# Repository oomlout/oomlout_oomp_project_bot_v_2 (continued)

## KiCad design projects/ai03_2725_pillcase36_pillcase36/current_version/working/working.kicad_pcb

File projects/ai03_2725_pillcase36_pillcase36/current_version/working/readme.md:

# pillcase36
 
## summary 
* id: ai03_2725_pillcase36_pillcase36
* user: ai03_2725
* name: pillcase36
* board: pillcase36
* repo: https://github.com/ai03-2725/pillcase36
* src_file_repo_kicad_pcb: pillcase36.kicad_pcb
* src_file_repo_kicad_pcb_link: https://github.com/ai03-2725/pillcase36/tree/master/pillcase36.kicad_pcb

* src_file_repo_sch: pillcase36.sch
* src_file_repo_sch_link: https://github.com/ai03-2725/pillcase36/tree/master/pillcase36.sch
* full details link: https://github.com/oomlout/oomlout_oomp_project_bot_v_2/tree/main/projects/ai03_2725_pillcase36_pillcase36/current_version/working  

## schematic  
  
[schematic (pdf)](working_schematic.pdf) 

## pcb  

[board (pdf)](working.pdf)  

## working_bom
| Id | Designator | Footprint | Quantity | Designation | Supplier and ref |  | None | 
| --- | --- | --- | --- | --- | --- | --- | --- | 
| 1 | D1,D2,D3,D4,D5,D7,D8,D9,D10,D11,D12,D13,D14,D15,D16,D17,D18,D19,D20,D21,D22,D23,D24,D25,D26,D27,D28,D29,D30,D31,D32,D33,D34,D35,D36,D6 | Diode_SMD_THT_N | 36 | D |  |  | [''] | 
| 2 | J1 | trrs_jack_aki_flip | 1 | AudioJack4_Ground |  |  | [''] | 
| 3 | R2,R1 | Resister_SMD_THT_N | 2 | 10K |  |  | [''] | 
| 4 | SW1,SW2,SW3,SW4,SW5,SW6,SW7,SW8,SW9,SW10,SW11,SW12,SW13,SW14,SW15,SW16,SW17,SW18,SW19,SW20,SW21,SW22,SW23,SW24,SW25,SW26,SW27,SW28,SW29,SW30,SW31,SW32,SW33,SW34,SW35,SW36 | key_switch_mx | 36 | SW_Push |  |  | [''] | 
| 5 | RESET | SW_PUSH_6mm_h5mm | 1 | SW_Push |  |  | [''] | 
| 6 | U1 | BlackPill | 1 | BlackPill |  |  | [''] | 
| 7 |  | Hole_5mm | 1 |  |  |  | [''] | 
| 8 | G***,G*** | pillcase36_logo | 2 | pillcase36_logo |  |  | [''] | 
| 9 | U2 | SOIC-8-N | 1 | 24LC00 |  |  | [''] | 
| 10 | SCL1 ,SDA1 | JP | 2 | SolderJumper_2_Bridged |  |  | [''] | 
| 11 | 0.1u | C_0603 | 1 | C |  |  | [''] | 

## bom_schematic
| Ref | Qnty | Value | Cmp name | Footprint | Description | Vendor | DNP | 
| --- | --- | --- | --- | --- | --- | --- | --- | 
| 0.1u1 | 1 | C | C | Capacitors_SMD:C_0603 | Unpolarized capacitor |  |  | 
| D1, D2, D3, D4, D5, D6, D7, D8, D9, D10, D11, D12, D13, D14, D15, D16, D17, D18, D19, D20, D21, D22, D23, D24, D25, D26, D27, D28, D29, D30, D31, D32, D33, D34, D35, D36 | 36 | D | D | pillcase36:Diode_SMD_THT_N | Diode |  |  | 
| J1 | 1 | AudioJack4_Ground | AudioJack4_Ground-Connector | pillcase36:trrs_jack_aki_flip |  |  |  | 
| JP13, JP14 | 2 | SolderJumper_2_Bridged | SolderJumper_2_Bridged | pillcase36:JP | Solder Jumper, 2-pole, closed/bridged |  |  | 
| R1, R2 | 2 | 10K | R | pillcase36:Resister_SMD_THT_N | Resistor |  |  | 
| SW1, SW2, SW3, SW4, SW5, SW6, SW7, SW8, SW9, SW10, SW11, SW12, SW13, SW14, SW15, SW16, SW17, SW18, SW19, SW20, SW21, SW22, SW23, SW24, SW25, SW26, SW27, SW28, SW29, SW30, SW31, SW32, SW33, SW34, SW35, SW36 | 36 | SW_Push | SW_Push | pillcase36:key_switch_mx | Push button switch, generic, two pins |  |  | 
| SW37 | 1 | SW_Push | SW_Push | Buttons_Switches_THT:SW_PUSH_6mm_h5mm | Push button switch, generic, two pins |  |  | 
| TP1 | 1 | B13 | TestPoint | Measurement_Points:Measurement_Point_Round-TH_Small | test point |  |  | 
| TP2 | 1 | B15 | TestPoint | Measurement_Points:Measurement_Point_Round-TH_Small | test point |  |  | 
| TP3 | 1 | A9 | TestPoint | Measurement_Points:Measurement_Point_Round-TH_Small | test point |  |  | 
| TP4 | 1 | A11 | TestPoint | Measurement_Points:Measurement_Point_Round-TH_Small | test point |  |  | 
| TP5 | 1 | A15 | TestPoint | Measurement_Points:Measurement_Point_Round-TH_Small | test point |  |  | 
| TP6 | 1 | B4 | TestPoint | Measurement_Points:Measurement_Point_Round-TH_Small | test point |  |  | 
| TP7 | 1 | B6 | TestPoint | Measurement_Points:Measurement_Point_Round-TH_Small | test point |  |  | 
| TP8 | 1 | B12 | TestPoint | Measurement_Points:Measurement_Point_Round-TH_Small | test point |  |  | 
| TP9 | 1 | B14 | TestPoint | Measurement_Points:Measurement_Point_Round-TH_Small | test point |  |  | 
| TP10 | 1 | A8 | TestPoint | Measurement_Points:Measurement_Point_Round-TH_Small | test point |  |  | 
| TP11 | 1 | A10 | TestPoint | Measurement_Points:Measurement_Point_Round-TH_Small | test point |  |  | 
| TP12 | 1 | A12 | TestPoint | Measurement_Points:Measurement_Point_Round-TH_Small | test point |  |  | 
| TP13 | 1 | B3 | TestPoint | Measurement_Points:Measurement_Point_Round-TH_Small | test point |  |  | 
| TP14 | 1 | B5 | TestPoint | Measurement_Points:Measurement_Point_Round-TH_Small | test point |  |  | 
| TP15 | 1 | B7 | TestPoint | Measurement_Points:Measurement_Point_Round-TH_Small | test point |  |  | 
| TP16 | 1 | B11 | TestPoint | Measurement_Points:Measurement_Point_Round-TH_Small | test point |  |  | 
| TP17 | 1 | B1 | TestPoint | Measurement_Points:Measurement_Point_Round-TH_Small | test point |  |  | 
| TP18 | 1 | A7 | TestPoint | Measurement_Points:Measurement_Point_Round-TH_Small | test point |  |  | 
| TP19 | 1 | A5 | TestPoint | Measurement_Points:Measurement_Point_Round-TH_Small | test point |  |  | 
| TP20 | 1 | A3 | TestPoint | Measurement_Points:Measurement_Point_Round-TH_Small | test point |  |  | 
| TP21 | 1 | A1 | TestPoint | Measurement_Points:Measurement_Point_Round-TH_Small | test point |  |  | 
| TP22 | 1 | C13 | TestPoint | Measurement_Points:Measurement_Point_Round-TH_Small | test point |  |  | 
| TP23 | 1 | B8 | TestPoint | Measurement_Points:Measurement_Point_Round-TH_Small | test point |  |  | 
| TP24 | 1 | B10 | TestPoint | Measurement_Points:Measurement_Point_Round-TH_Small | test point |  |  | 
| TP25 | 1 | B0 | TestPoint | Measurement_Points:Measurement_Point_Round-TH_Small | test point |  |  | 
| TP26 | 1 | A6 | TestPoint | Measurement_Points:Measurement_Point_Round-TH_Small | test point |  |  | 
| TP27 | 1 | A4 | TestPoint | Measurement_Points:Measurement_Point_Round-TH_Small | test point |  |  | 
| TP28 | 1 | A2 | TestPoint | Measurement_Points:Measurement_Point_Round-TH_Small | test point |  |  | 
| TP29 | 1 | A0 | TestPoint | Measurement_Points:Measurement_Point_Round-TH_Small | test point |  |  | 
| TP30 | 1 | B9 | TestPoint | Measurement_Points:Measurement_Point_Round-TH_Small | test point |  |  | 
| TP31 | 1 | R1 | TestPoint | Measurement_Points:Measurement_Point_Round-TH_Small | test point |  |  | 
| TP32 | 1 | R2 | TestPoint | Measurement_Points:Measurement_Point_Round-TH_Small | test point |  |  | 
| U1 | 1 | BlackPill | BlackPill-pillcase36 | pillcase36:BlackPill |  |  |  | 
| U2 | 1 | 24LC00 | 24LC00 | SMD_Packages:SOIC-8-N | I2C Serial EEPROM, 128 Bits, DIP-8/SOIC-8/TSSOP-8/DFN-8 |  |  |

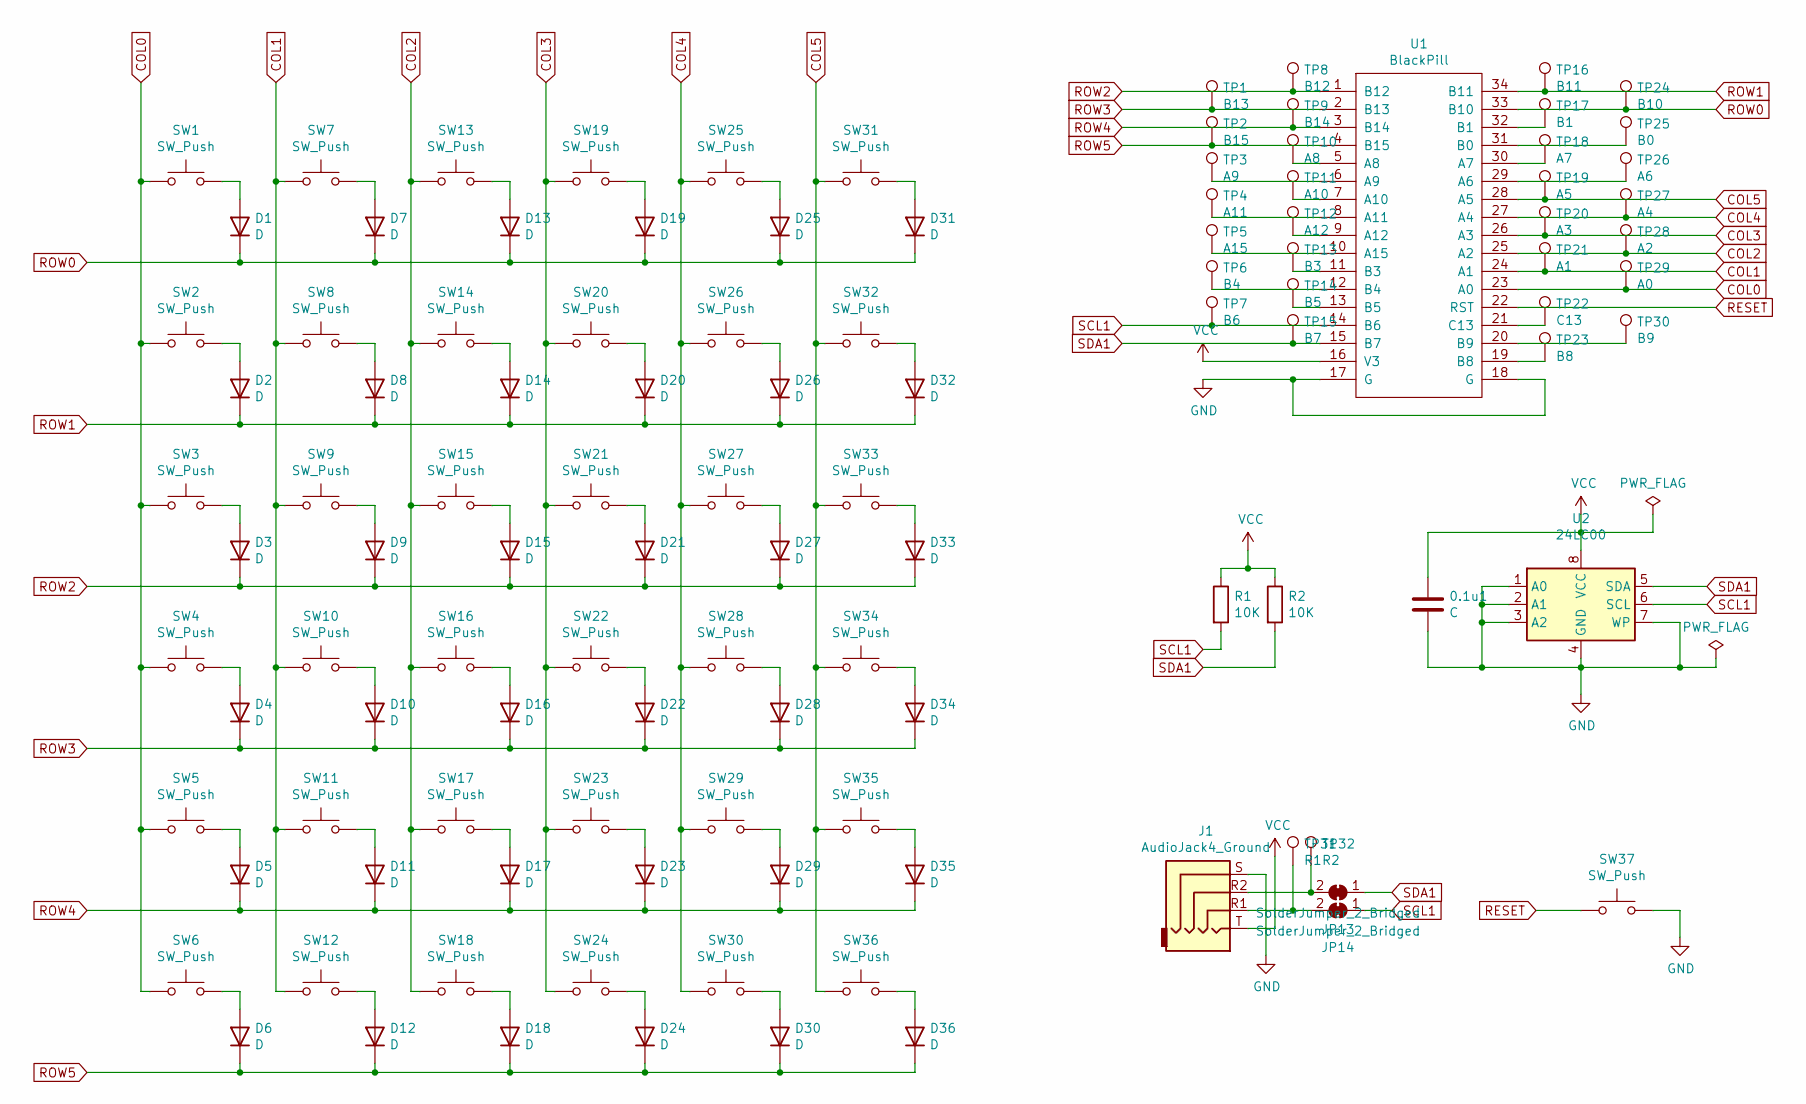
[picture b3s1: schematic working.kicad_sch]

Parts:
0.1u1: C; C_0603
D1, D2, D3, D4, D5, D6, D7, D8, D9, D10, D11, D12, D13, D14, D15, D16, D17, D18, D19, D20, D21, D22, D23, D24, D25, D26, D27, D28, D29, D30, D31, D32, D33, D34, D35, D36: D; Diode_SMD_THT_N
J1: AudioJack4_Ground; trrs_jack_aki_flip
JP13, JP14: SolderJumper_2_Bridged; JP
R1, R2: 10K; Resister_SMD_THT_N
SW1, SW2, SW3, SW4, SW5, SW6, SW7, SW8, SW9, SW10, SW11, SW12, SW13, SW14, SW15, SW16, SW17, SW18, SW19, SW20, SW21, SW22, SW23, SW24, SW25, SW26, SW27, SW28, SW29, SW30, SW31, SW32, SW33, SW34, SW35, SW36: SW_Push; key_switch_mx
SW37: SW_Push; SW_PUSH_6mm_h5mm
TP1: B13; Measurement_Point_Round-TH_Small
TP2: B15; Measurement_Point_Round-TH_Small
TP3: A9; Measurement_Point_Round-TH_Small
TP4: A11; Measurement_Point_Round-TH_Small
TP5: A15; Measurement_Point_Round-TH_Small
TP6: B4; Measurement_Point_Round-TH_Small
TP7: B6; Measurement_Point_Round-TH_Small
TP8: B12; Measurement_Point_Round-TH_Small
TP9: B14; Measurement_Point_Round-TH_Small
TP10: A8; Measurement_Point_Round-TH_Small
TP11: A10; Measurement_Point_Round-TH_Small
TP12: A12; Measurement_Point_Round-TH_Small
TP13: B3; Measurement_Point_Round-TH_Small
TP14: B5; Measurement_Point_Round-TH_Small
TP15: B7; Measurement_Point_Round-TH_Small
TP16: B11; Measurement_Point_Round-TH_Small
TP17: B1; Measurement_Point_Round-TH_Small
TP18: A7; Measurement_Point_Round-TH_Small
TP19: A5; Measurement_Point_Round-TH_Small
TP20: A3; Measurement_Point_Round-TH_Small
TP21: A1; Measurement_Point_Round-TH_Small
TP22: C13; Measurement_Point_Round-TH_Small
TP23: B8; Measurement_Point_Round-TH_Small
TP24: B10; Measurement_Point_Round-TH_Small
TP25: B0; Measurement_Point_Round-TH_Small
TP26: A6; Measurement_Point_Round-TH_Small
TP27: A4; Measurement_Point_Round-TH_Small
TP28: A2; Measurement_Point_Round-TH_Small
TP29: A0; Measurement_Point_Round-TH_Small
TP30: B9; Measurement_Point_Round-TH_Small
TP31: R1; Measurement_Point_Round-TH_Small
TP32: R2; Measurement_Point_Round-TH_Small
U1: BlackPill
U2: 24LC00; SOIC-8-N

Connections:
COL0: SW1.1, SW2.1, SW3.1, SW4.1, SW5.1, SW6.1, TP29.1, U1.23 (A0)
COL1: SW7.1, SW8.1, SW9.1, SW10.1, SW11.1, SW12.1, TP21.1, U1.24 (A1)
COL2: SW13.1, SW14.1, SW15.1, SW16.1, SW17.1, SW18.1, TP28.1, U1.25 (A2)
COL3: SW19.1, SW20.1, SW21.1, SW22.1, SW23.1, SW24.1, TP20.1, U1.26 (A3)
COL4: SW25.1, SW26.1, SW27.1, SW28.1, SW29.1, SW30.1, TP27.1, U1.27 (A4)
COL5: SW31.1, SW32.1, SW33.1, SW34.1, SW35.1, SW36.1, TP19.1, U1.28 (A5)
GND: 0.1u1.2, J1.S, SW37.2, U1.17 (G), U1.18 (G), U2.1 (A0), U2.2 (A1), U2.3 (A2), U2.4 (GND), U2.7 (WP); also elsewhere on the board
unnamed: D1.2 (A), SW1.2
unnamed: D2.2 (A), SW2.2
unnamed: D3.2 (A), SW3.2
unnamed: D4.2 (A), SW4.2
unnamed: D5.2 (A), SW5.2
unnamed: D6.2 (A), SW6.2
unnamed: D7.2 (A), SW7.2
unnamed: D8.2 (A), SW8.2
unnamed: D9.2 (A), SW9.2
unnamed: D10.2 (A), SW10.2
unnamed: D11.2 (A), SW11.2
unnamed: D12.2 (A), SW12.2
unnamed: D13.2 (A), SW13.2
unnamed: D14.2 (A), SW14.2
unnamed: D15.2 (A), SW15.2
unnamed: D16.2 (A), SW16.2
unnamed: D17.2 (A), SW17.2
unnamed: D18.2 (A), SW18.2
unnamed: D19.2 (A), SW19.2
unnamed: D20.2 (A), SW20.2
unnamed: D21.2 (A), SW21.2
unnamed: D22.2 (A), SW22.2
unnamed: D23.2 (A), SW23.2
unnamed: D24.2 (A), SW24.2
unnamed: D25.2 (A), SW25.2
unnamed: D26.2 (A), SW26.2
unnamed: D27.2 (A), SW27.2
unnamed: D28.2 (A), SW28.2
unnamed: D29.2 (A), SW29.2
unnamed: D30.2 (A), SW30.2
unnamed: D31.2 (A), SW31.2
unnamed: D32.2 (A), SW32.2
unnamed: D33.2 (A), SW33.2
unnamed: D34.2 (A), SW34.2
unnamed: D35.2 (A), SW35.2
unnamed: D36.2 (A), SW36.2
unnamed 43: J1.R2, JP13.2 (B), TP32.1; also elsewhere on the board
unnamed: TP3.1, U1.6 (A9)
unnamed: TP4.1, U1.8 (A11)
unnamed: TP5.1, U1.10 (A15)
unnamed: TP6.1, U1.12 (B4)
unnamed: TP10.1, U1.5 (A8)
unnamed: TP11.1, U1.7 (A10)
unnamed: TP12.1, U1.9 (A12)
unnamed: TP13.1, U1.11 (B3)
unnamed: TP14.1, U1.13 (B5)
unnamed: TP17.1, U1.32 (B1)
unnamed: TP18.1, U1.30 (A7)
unnamed: TP22.1, U1.21 (C13)
unnamed: TP23.1, U1.19 (B8)
unnamed: TP25.1, U1.31 (B0)
unnamed: TP26.1, U1.29 (A6)
unnamed: TP30.1, U1.20 (B9)
RESET: SW37.1, U1.22 (RST); also elsewhere on the board
ROW0: D1.1 (K), D7.1 (K), D13.1 (K), D19.1 (K), D25.1 (K), D31.1 (K), TP24.1, U1.33 (B10)
ROW1: D2.1 (K), D8.1 (K), D14.1 (K), D20.1 (K), D26.1 (K), D32.1 (K), TP16.1, U1.34 (B11)
ROW2: D3.1 (K), D9.1 (K), D15.1 (K), D21.1 (K), D27.1 (K), D33.1 (K), TP8.1, U1.1 (B12)
ROW3: D4.1 (K), D10.1 (K), D16.1 (K), D22.1 (K), D28.1 (K), D34.1 (K), TP1.1, U1.2 (B13)
ROW4: D5.1 (K), D11.1 (K), D17.1 (K), D23.1 (K), D29.1 (K), D35.1 (K), TP9.1, U1.3 (B14)
ROW5: D6.1 (K), D12.1 (K), D18.1 (K), D24.1 (K), D30.1 (K), D36.1 (K), TP2.1, U1.4 (B15)
SCL1: JP14.1 (A), R1.2, TP7.1, U1.14 (B6), U2.6 (SCL); also elsewhere on the board
SDA1: JP13.1 (A), R2.2, TP15.1, U1.15 (B7), U2.5 (SDA); also elsewhere on the board

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
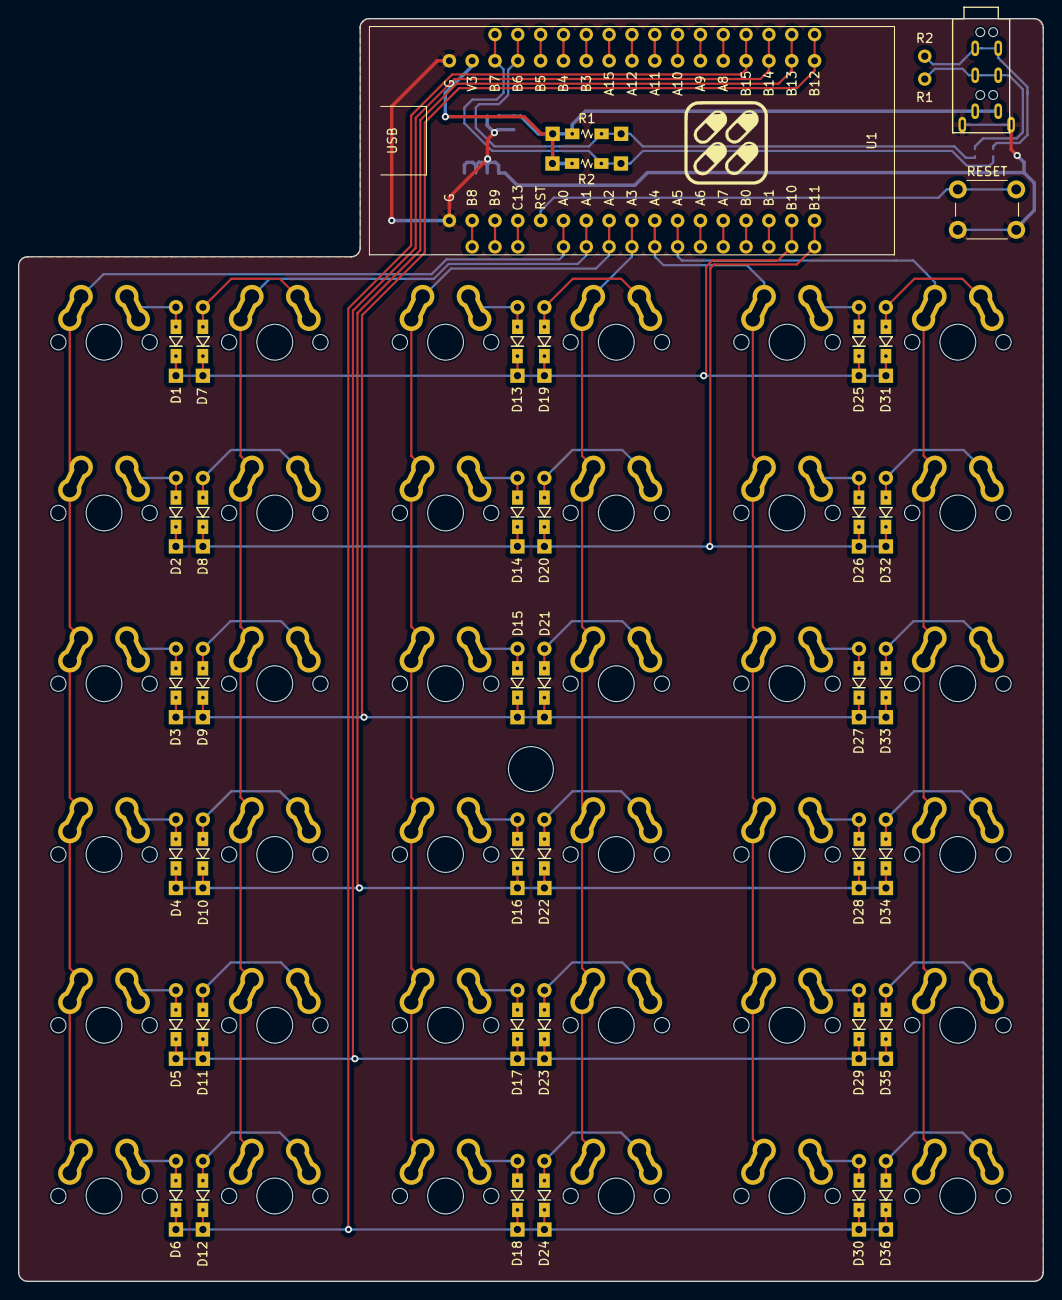
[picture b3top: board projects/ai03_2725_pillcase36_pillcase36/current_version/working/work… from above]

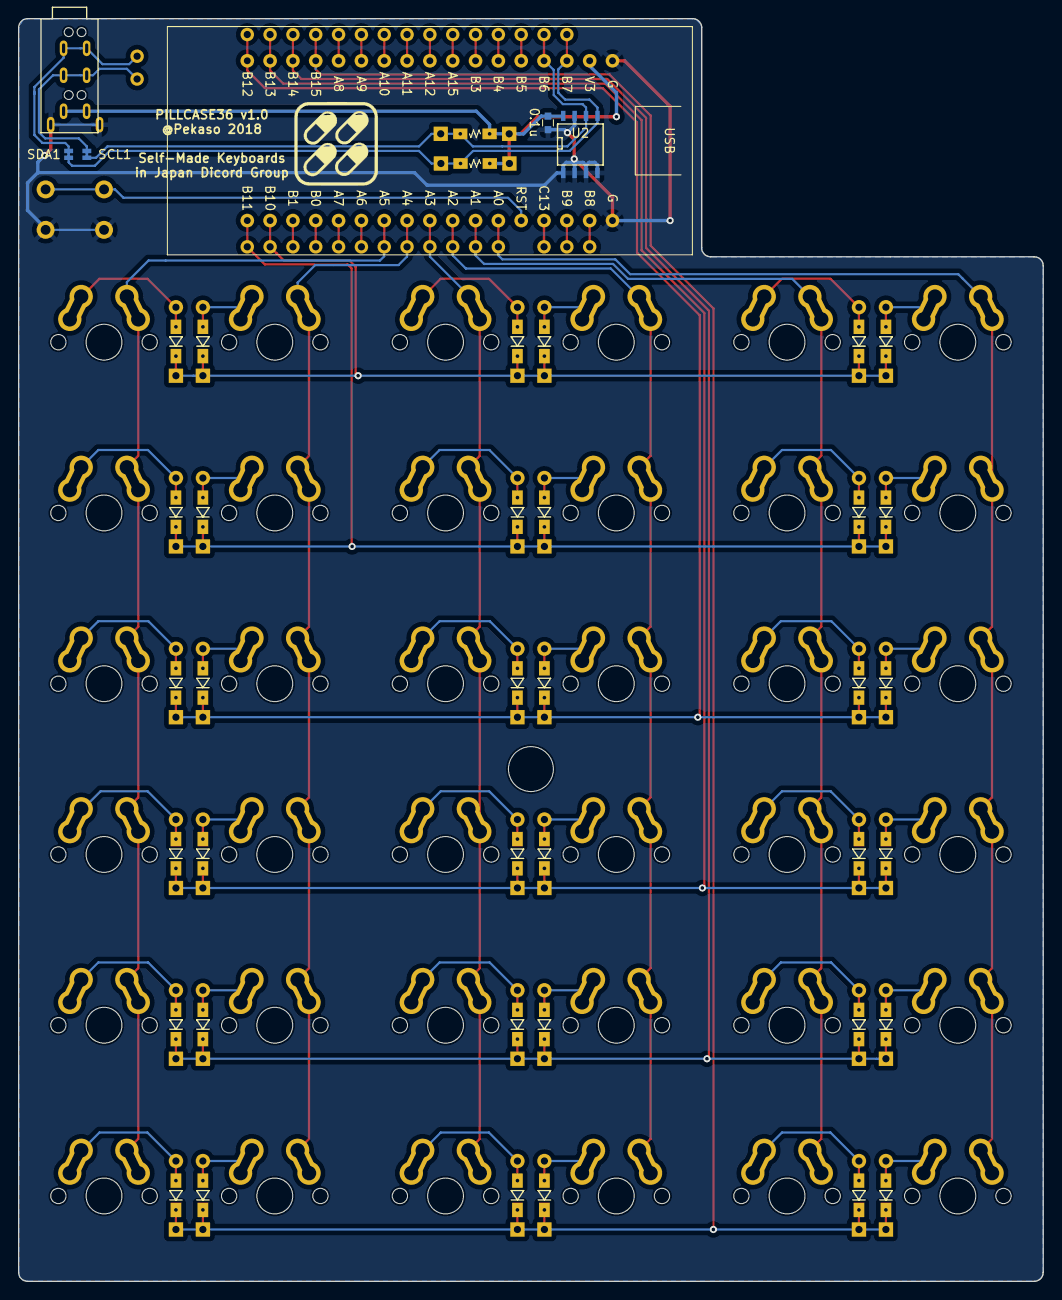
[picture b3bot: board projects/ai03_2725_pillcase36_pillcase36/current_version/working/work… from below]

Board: 2 copper layers, 114.0 x 140.5 mm, 113 parts (4 on the bottom side), 71 nets.

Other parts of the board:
0.1u: C; C_0603
R1#2: 10K; Resister_SMD_THT_N
R2#2: R2; Measurement_Point_Round-TH_Small
RESET: SW_Push; SW_PUSH_6mm_h5mm
SCL1 : SolderJumper_2_Bridged; JP
SDA1: SolderJumper_2_Bridged; JP

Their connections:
GND: 0.1u.2, RESET.2; also elsewhere on the board
unnamed 43: R2#2.1, SDA1.2; also elsewhere on the board
RESET: RESET.1; also elsewhere on the board
SCL1: R1#2.2, SCL1.1; also elsewhere on the board
SDA1: SDA1.1; also elsewhere on the board

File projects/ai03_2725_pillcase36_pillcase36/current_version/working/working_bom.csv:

"Id";"Designator";"Footprint";"Quantity";"Designation";"Supplier and ref";
1;"D1,D2,D3,D4,D5,D7,D8,D9,D10,D11,D12,D13,D14,D15,D16,D17,D18,D19,D20,D21,D22,D23,D24,D25,D26,D27,D28,D29,D30,D31,D32,D33,D34,D35,D36,D6";"Diode_SMD_THT_N";36;"D";;;
2;"J1";"trrs_jack_aki_flip";1;"AudioJack4_Ground";;;
3;"R2,R1";"Resister_SMD_THT_N";2;"10K";;;
4;"SW1,SW2,SW3,SW4,SW5,SW6,SW7,SW8,SW9,SW10,SW11,SW12,SW13,SW14,SW15,SW16,SW17,SW18,SW19,SW20,SW21,SW22,SW23,SW24,SW25,SW26,SW27,SW28,SW29,SW30,SW31,SW32,SW33,SW34,SW35,SW36";"key_switch_mx";36;"SW_Push";;;
5;"RESET";"SW_PUSH_6mm_h5mm";1;"SW_Push";;;
6;"U1";"BlackPill";1;"BlackPill";;;
7;"";"Hole_5mm";1;"";;;
8;"G***,G***";"pillcase36_logo";2;"pillcase36_logo";;;
9;"U2";"SOIC-8-N";1;"24LC00";;;
10;"SCL1 ,SDA1";"JP";2;"SolderJumper_2_Bridged";;;
11;"0.1u";"C_0603";1;"C";;;

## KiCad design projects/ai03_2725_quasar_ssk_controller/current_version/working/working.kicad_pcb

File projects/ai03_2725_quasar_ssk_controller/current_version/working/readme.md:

# quasar
 
## summary 
* id: ai03_2725_quasar_ssk_controller
* user: ai03_2725
* name: quasar
* board: ssk_controller
* repo: https://github.com/ai03-2725/Quasar
* src_file_repo_kicad_pcb: ssk-controller.kicad_pcb
* src_file_repo_kicad_pcb_link: https://github.com/ai03-2725/Quasar/tree/master/ssk-controller.kicad_pcb

* src_file_repo_sch: ssk-controller.sch
* src_file_repo_sch_link: https://github.com/ai03-2725/Quasar/tree/master/ssk-controller.sch
* full details link: https://github.com/oomlout/oomlout_oomp_project_bot_v_2/tree/main/projects/ai03_2725_quasar_ssk_controller/current_version/working  

## schematic  
  
[schematic (pdf)](working_schematic.pdf) 

## pcb  

[board (pdf)](working.pdf)  

## working_bom
| Id | Designator | Footprint | Quantity | Designation | Supplier and ref |  | None | 
| --- | --- | --- | --- | --- | --- | --- | --- | 
| 1 | F1 | Fuse_1206_3216Metric | 1 | 500mA |  |  | [''] | 
| 2 | J1 | PinHeader_1x16_P2.54mm_Vertical | 1 | Conn_01x16 |  |  | [''] | 
| 3 | R67,R68 | R_0805_2012Metric | 2 | 22 |  |  | [''] | 
| 4 | R70,R1 | R_0805_2012Metric | 2 | 10k |  |  | [''] | 
| 5 | R71 | R_0805_2012Metric | 1 | 1k |  |  | [''] | 
| 6 | SW1 | SKQG-1155865 | 1 | SW_Push |  |  | [''] | 
| 7 | Y1 | Crystal_SMD_3225-4Pin_3.2x2.5mm | 1 | 16Mhz |  |  | [''] | 
| 8 | U1 | TQFP-44_10x10mm_P0.8mm | 1 | ATmega32U4-AU |  |  | [''] | 
| 9 | J2 | PinHeader_1x08_P2.54mm_Vertical | 1 | Conn_01x08 |  |  | [''] | 
| 10 | C2 | C_0805_2012Metric | 1 | 10uF |  |  | [''] | 
| 11 | C3,C4,C5 | C_0805_2012Metric | 3 | 0.1uF |  |  | [''] | 
| 12 | C6 | C_0805_2012Metric | 1 | 1uF |  |  | [''] | 
| 13 | C7,C8 | C_0805_2012Metric | 2 | 22pF |  |  | [''] | 
| 14 | J3 | PinHeader_1x01_P2.54mm_Vertical | 1 | Conn_01x01 |  |  | [''] | 
| 15 | G*** | Quasar-Logo | 1 | LOGO |  |  | [''] | 
| 16 | G*** | Quasar-Desc | 1 | LOGO |  |  | [''] | 
| 17 | G***,G*** | ai-ring-6mm-Combined | 2 | LOGO |  |  | [''] | 
| 18 | J4 | TE-292304-2 | 1 | USB_B |  |  | [''] | 
| 19 | U2 | SOT143B | 1 | PRTR5V0U2X |  |  | [''] | 
| 20 | J5 | PinHeader_1x02_P2.54mm_Vertical | 1 | Solenoid |  |  | [''] | 
| 21 | R2 | R_0805_2012Metric | 1 | 100 |  |  | [''] | 
| 22 | C1 | C_0805_2012Metric | 1 | 4.7nF |  |  | [''] | 
| 23 | R3 | R_0805_2012Metric | 1 | 1M |  |  | [''] | 
| 24 | D1 | D_SOD-123 | 1 | 1N4007 |  |  | [''] | 
| 25 | Q1 | SOT-23 | 1 | Q_NMOS_GSD |  |  | [''] | 
| 26 | C9 | CP_EIA-3216-18_Kemet-A | 1 | 1uF |  |  | [''] | 

## bom_schematic
| Ref | Qnty | Value | Cmp name | Footprint | Description | Vendor | DNP | 
| --- | --- | --- | --- | --- | --- | --- | --- | 
| C1 | 1 | 4.7nF | C_Small | Capacitor_SMD:C_0805_2012Metric | Unpolarized capacitor, small symbol |  |  | 
| C2 | 1 | 10uF | C_Small | Capacitor_SMD:C_0805_2012Metric | Unpolarized capacitor, small symbol |  |  | 
| C3, C4, C5 | 3 | 0.1uF | C_Small | Capacitor_SMD:C_0805_2012Metric | Unpolarized capacitor, small symbol |  |  | 
| C6 | 1 | 1uF | C_Small | Capacitor_SMD:C_0805_2012Metric | Unpolarized capacitor, small symbol |  |  | 
| C7, C8 | 2 | 22pF | C_Small | Capacitor_SMD:C_0805_2012Metric | Unpolarized capacitor, small symbol |  |  | 
| C9 | 1 | 1uF | CP_Small-Device | Capacitor_Tantalum_SMD:CP_EIA-3216-18_Kemet-A |  |  |  | 
| D1 | 1 | 1N4007 | D_Small | Diode_SMD:D_SOD-123 | Diode, small symbol |  |  | 
| F1 | 1 | 500mA | Polyfuse_Small | Fuse:Fuse_1206_3216Metric | Resettable fuse, polymeric positive temperature coefficient, small symbol |  |  | 
| J1 | 1 | Conn_01x16 | Conn_01x16 | Connector_PinHeader_2.54mm:PinHeader_1x16_P2.54mm_Vertical | Generic connector, single row, 01x16, script generated (kicad-library-utils/schlib/autogen/connector/) |  |  | 
| J2 | 1 | Conn_01x08 | Conn_01x08 | Connector_PinHeader_2.54mm:PinHeader_1x08_P2.54mm_Vertical | Generic connector, single row, 01x08, script generated (kicad-library-utils/schlib/autogen/connector/) |  |  | 
| J3 | 1 | Conn_01x01 | Conn_01x01 | Connector_PinHeader_2.54mm:PinHeader_1x01_P2.54mm_Vertical | Generic connector, single row, 01x01, script generated (kicad-library-utils/schlib/autogen/connector/) |  |  | 
| J4 | 1 | USB_B | USB_B-Connector | locallib:TE-292304-2 |  |  |  | 
| J5 | 1 | Solenoid | Conn_01x02 | Connector_PinHeader_2.54mm:PinHeader_1x02_P2.54mm_Vertical | Generic connector, single row, 01x02, script generated (kicad-library-utils/schlib/autogen/connector/) |  |  | 
| Q1 | 1 | Q_NMOS_GSD | Q_NMOS_GSD | Package_TO_SOT_SMD:SOT-23 | N-MOSFET transistor, gate/source/drain |  |  | 
| R1, R70 | 2 | 10k | R_Small | Resistor_SMD:R_0805_2012Metric | Resistor, small symbol |  |  | 
| R2 | 1 | 100 | R_Small | Resistor_SMD:R_0805_2012Metric | Resistor, small symbol |  |  | 
| R3 | 1 | 1M | R_Small | Resistor_SMD:R_0805_2012Metric | Resistor, small symbol |  |  | 
| R67, R68 | 2 | 22 | R_Small | Resistor_SMD:R_0805_2012Metric | Resistor, small symbol |  |  | 
| R71 | 1 | 1k | R_Small | Resistor_SMD:R_0805_2012Metric | Resistor, small symbol |  |  | 
| SW1 | 1 | SW_Push | SW_Push | random-keyboard-parts:SKQG-1155865 | Push button switch, generic, two pins |  |  | 
| U1 | 1 | ATmega32U4-AU | ATmega32U4-AU-MCU_Microchip_ATmega | Package_QFP:TQFP-44_10x10mm_P0.8mm |  |  |  | 
| U2 | 1 | PRTR5V0U2X | PRTR5V0U2X | locallib:SOT143B |  |  |  | 
| Y1 | 1 | 16Mhz | Crystal_GND24 | Crystal:Crystal_SMD_3225-4Pin_3.2x2.5mm | Four pin crystal, GND on pins 2 and 4 |  |  |

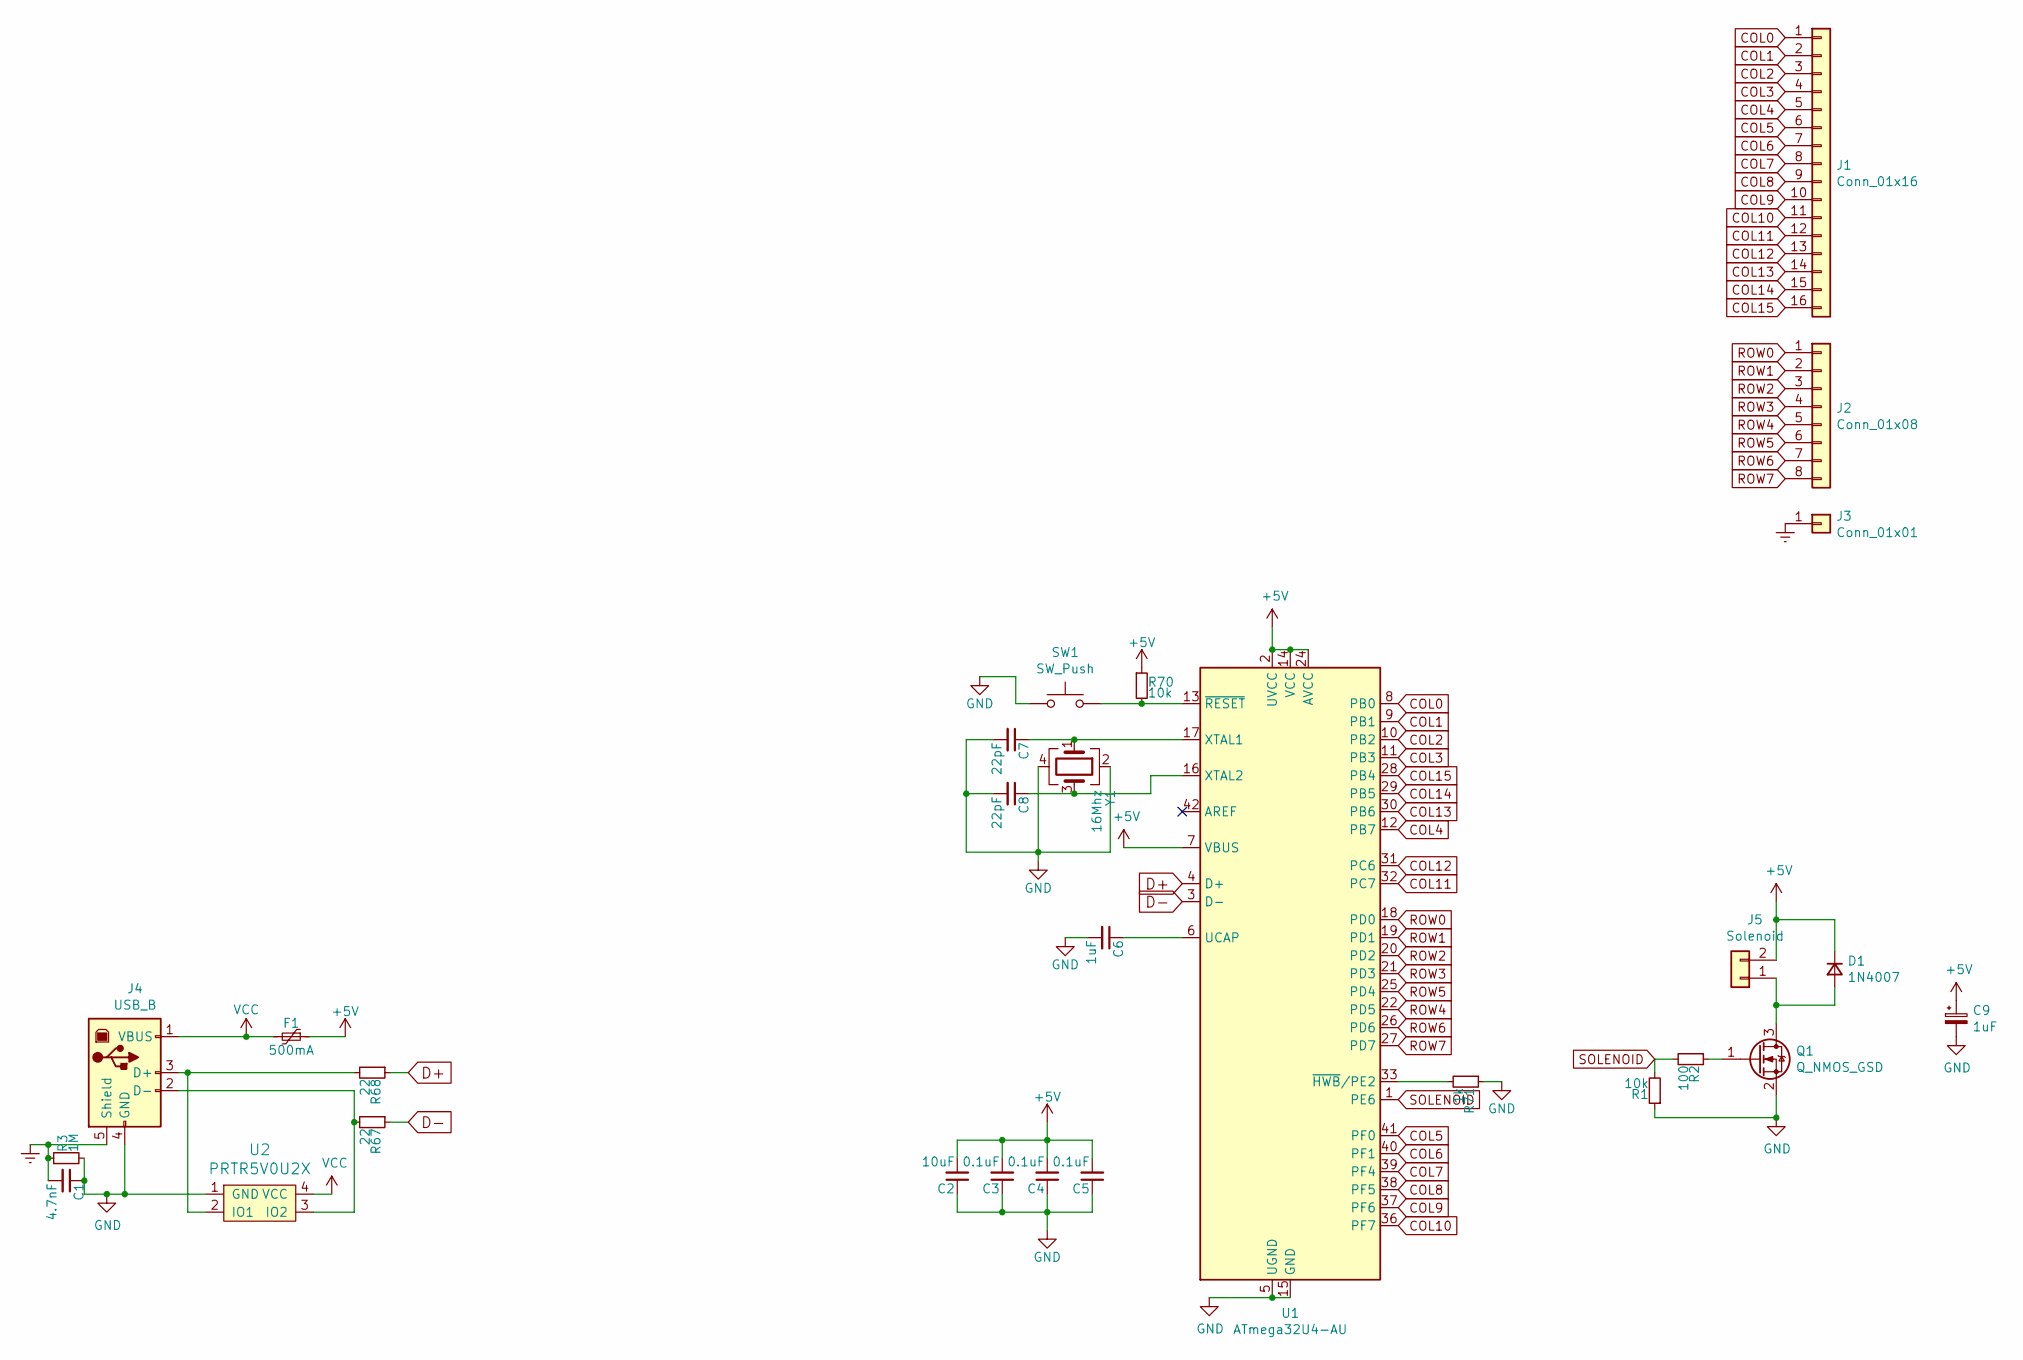
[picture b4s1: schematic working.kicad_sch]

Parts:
C1: 4.7nF; C_0805_2012Metric
C2: 10uF; C_0805_2012Metric
C3, C4, C5: 0.1uF; C_0805_2012Metric
C6: 1uF; C_0805_2012Metric
C7, C8: 22pF; C_0805_2012Metric
C9: 1uF; CP_EIA-3216-18_Kemet-A
D1: 1N4007; D_SOD-123
F1: 500mA; Fuse_1206_3216Metric
J1: Conn_01x16; PinHeader_1x16_P2.54mm_Vertical
J2: Conn_01x08; PinHeader_1x08_P2.54mm_Vertical
J3: Conn_01x01; PinHeader_1x01_P2.54mm_Vertical
J4: USB_B; TE-292304-2
J5: Solenoid; PinHeader_1x02_P2.54mm_Vertical
Q1: Q_NMOS_GSD; SOT-23
R1, R70: 10k; R_0805_2012Metric
R2: 100; R_0805_2012Metric
R3: 1M; R_0805_2012Metric
R67, R68: 22; R_0805_2012Metric
R71: 1k; R_0805_2012Metric
SW1: SW_Push; SKQG-1155865
U1: ATmega32U4-AU; TQFP-44_10x10mm_P0.8mm
U2: PRTR5V0U2X; SOT143B
Y1: 16Mhz; Crystal_SMD_3225-4Pin_3.2x2.5mm

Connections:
+5V: C2.2, C3.2, C4.2, C5.2, C9.1, D1.1 (K), F1.1, J5.2, R70.1, U1.2 (UVCC), U1.7 (VBUS), U1.14 (VCC), U1.24 (AVCC), U1.34 (VCC), U1.44 (AVCC)
COL0: J1.1, U1.8 (PB0)
COL1: J1.2, U1.9 (PB1)
COL2: J1.3, U1.10 (PB2)
COL3: J1.4, U1.11 (PB3)
COL4: J1.5, U1.12 (PB7)
COL5: J1.6, U1.41 (PF0)
COL6: J1.7, U1.40 (PF1)
COL7: J1.8, U1.39 (PF4)
COL8: J1.9, U1.38 (PF5)
COL9: J1.10, U1.37 (PF6)
COL10: J1.11, U1.36 (PF7)
COL11: J1.12, U1.32 (PC7)
COL12: J1.13, U1.31 (PC6)
COL13: J1.14, U1.30 (PB6)
COL14: J1.15, U1.29 (PB5)
COL15: J1.16, U1.28 (PB4)
D+: R68.1, U1.4 (D+)
D-: R67.1, U1.3 (D-)
Earth: C1.2, J3.1, J4.5 (Shield), R3.1
GND: C1.1, C2.1, C3.1, C4.1, C5.1, C6.2, C7.2, C8.2, C9.2, J4.4 (GND), Q1.2 (S), R1.1, R3.2, R71.1, SW1.1, U1.5 (UGND), U1.15 (GND), U1.23 (GND), U1.35 (GND), U1.43 (GND), U2.1 (GND), Y1.2, Y1.4
unnamed: C6.1, U1.6 (UCAP)
unnamed: C7.1, U1.17 (XTAL1), Y1.1
unnamed: C8.1, U1.16 (XTAL2), Y1.3
unnamed: D1.2 (A), J5.1, Q1.3 (D)
unnamed: J4.2 (D-), R67.2, U2.3 (IO2)
unnamed: J4.3 (D+), R68.2, U2.2 (IO1)
unnamed: Q1.1 (G), R2.1
unnamed: R70.2, SW1.2, U1.13 (~RESET)
unnamed: R71.2, U1.33 (~HWB/PE2)
ROW0: J2.1, U1.18 (PD0)
ROW1: J2.2, U1.19 (PD1)
ROW2: J2.3, U1.20 (PD2)
ROW3: J2.4, U1.21 (PD3)
ROW4: J2.5, U1.22 (PD5)
ROW5: J2.6, U1.25 (PD4)
ROW6: J2.7, U1.26 (PD6)
ROW7: J2.8, U1.27 (PD7)
SOLENOID: R1.2, R2.2, U1.1 (PE6)
VCC: F1.2, J4.1 (VBUS), U2.4 (VCC)

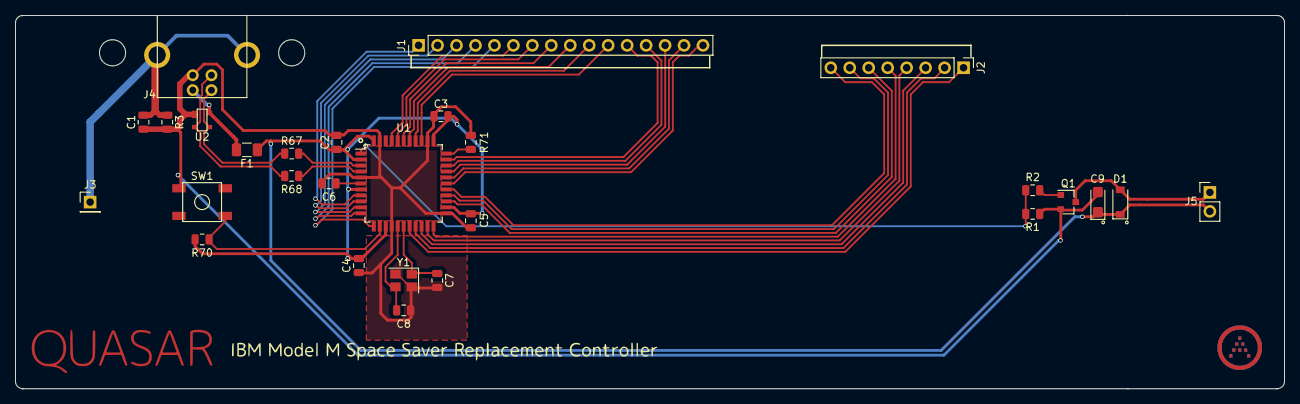
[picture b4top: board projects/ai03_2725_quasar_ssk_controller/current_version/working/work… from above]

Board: 2 copper layers, 170.0 x 50.0 mm, 28 parts (0 on the bottom side), 40 nets.

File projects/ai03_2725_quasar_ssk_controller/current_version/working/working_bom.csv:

"Id";"Designator";"Footprint";"Quantity";"Designation";"Supplier and ref";
1;"F1";"Fuse_1206_3216Metric";1;"500mA";;;
2;"J1";"PinHeader_1x16_P2.54mm_Vertical";1;"Conn_01x16";;;
3;"R67,R68";"R_0805_2012Metric";2;"22";;;
4;"R70,R1";"R_0805_2012Metric";2;"10k";;;
5;"R71";"R_0805_2012Metric";1;"1k";;;
6;"SW1";"SKQG-1155865";1;"SW_Push";;;
7;"Y1";"Crystal_SMD_3225-4Pin_3.2x2.5mm";1;"16Mhz";;;
8;"U1";"TQFP-44_10x10mm_P0.8mm";1;"ATmega32U4-AU";;;
9;"J2";"PinHeader_1x08_P2.54mm_Vertical";1;"Conn_01x08";;;
10;"C2";"C_0805_2012Metric";1;"10uF";;;
11;"C3,C4,C5";"C_0805_2012Metric";3;"0.1uF";;;
12;"C6";"C_0805_2012Metric";1;"1uF";;;
13;"C7,C8";"C_0805_2012Metric";2;"22pF";;;
14;"J3";"PinHeader_1x01_P2.54mm_Vertical";1;"Conn_01x01";;;
15;"G***";"Quasar-Logo";1;"LOGO";;;
16;"G***";"Quasar-Desc";1;"LOGO";;;
17;"G***,G***";"ai-ring-6mm-Combined";2;"LOGO";;;
18;"J4";"TE-292304-2";1;"USB_B";;;
19;"U2";"SOT143B";1;"PRTR5V0U2X";;;
20;"J5";"PinHeader_1x02_P2.54mm_Vertical";1;"Solenoid";;;
21;"R2";"R_0805_2012Metric";1;"100";;;
22;"C1";"C_0805_2012Metric";1;"4.7nF";;;
23;"R3";"R_0805_2012Metric";1;"1M";;;
24;"D1";"D_SOD-123";1;"1N4007";;;
25;"Q1";"SOT-23";1;"Q_NMOS_GSD";;;
26;"C9";"CP_EIA-3216-18_Kemet-A";1;"1uF";;;

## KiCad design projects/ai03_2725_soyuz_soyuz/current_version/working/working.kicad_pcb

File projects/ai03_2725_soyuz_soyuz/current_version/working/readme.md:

# soyuz
 
## summary 
* id: ai03_2725_soyuz_soyuz
* user: ai03_2725
* name: soyuz
* board: soyuz
* repo: https://github.com/ai03-2725/Soyuz
* src_file_repo_kicad_pcb: Soyuz.kicad_pcb
* src_file_repo_kicad_pcb_link: https://github.com/ai03-2725/Soyuz/tree/master/Soyuz.kicad_pcb

* src_file_repo_sch: Soyuz.sch
* src_file_repo_sch_link: https://github.com/ai03-2725/Soyuz/tree/master/Soyuz.sch
* full details link: https://github.com/oomlout/oomlout_oomp_project_bot_v_2/tree/main/projects/ai03_2725_soyuz_soyuz/current_version/working  

## schematic  
  
[schematic (pdf)](working_schematic.pdf) 

## pcb  

[board (pdf)](working.pdf)  

## working_bom
| Id | Designator | Footprint | Quantity | Designation | Supplier and ref |  | None | 
| --- | --- | --- | --- | --- | --- | --- | --- | 
| 1 | G*** | soyuz-logo-30mm | 1 | LOGO |  |  | [''] | 
| 2 | MX1,MX2,MX3,MX4,MX5,MX6,MX7,MX8,MX10,MX11,MX12,MX13,MX14,MX15,MX16,MX17,MX19,MX20,MX21,MX22 | MX-1U-NoLED | 20 | MX-1U |  |  | [''] | 
| 3 | MX9,MX18,MX23 | MX-2U-ReversedStabilizers-NoLED | 3 | MX-2U |  |  | [''] | 
| 4 | MOUSEBITE1,MOUSEBITE2,MOUSEBITE3,MOUSEBITE4,MOUSEBITE5,MOUSEBITE6,MOUSEBITE7,MOUSEBITE8 | breakaway-mousebites | 8 | Mousebites |  |  | [''] | 
| 5 | O1 | outline | 1 | Outline |  |  | [''] | 
| 6 | D1,D2,D3,D4,D5,D7,D8,D9,D10,D11,D12,D13,D14,D15,D16,D17,D18,D19,D20,D6 | D_DO-35_SOD27_P7.62mm_Horizontal | 20 | 1N4148 |  |  | [''] | 
| 7 | U1 | ProMicro-EnforcedTop | 1 | ProMicro |  |  | [''] | 
| 8 | G*** | ai-4.8-silk | 1 | LOGO |  |  | [''] | 
| 9 | G*** | ai-ring-25mm-mask | 1 | LOGO |  |  | [''] | 
| 10 | SW1 | PushButton_6x6mm_TH_Pretty | 1 | SW_Push |  |  | [''] | 
| 11 | G*** | soyuz-by-ai03 | 1 | LOGO |  |  | [''] | 

## bom_schematic
| Ref | Qnty | Value | Cmp name | Footprint | Description | Vendor | DNP | 
| --- | --- | --- | --- | --- | --- | --- | --- | 
| D1, D2, D3, D4, D5, D6, D7, D8, D9, D10, D11, D12, D13, D14, D15, D16, D17, D18, D19, D20 | 20 | 1N4148 | D_Small | Diodes_THT:D_DO-35_SOD27_P7.62mm_Horizontal | Diode, small symbol |  |  | 
| MOUSEBITE1, MOUSEBITE2, MOUSEBITE3, MOUSEBITE4, MOUSEBITE5, MOUSEBITE6, MOUSEBITE7, MOUSEBITE8 | 8 | Mousebites | Conn_01x01 | random-keyboard-parts:breakaway-mousebites | Generic connector, single row, 01x01, script generated (kicad-library-utils/schlib/autogen/connector/) |  |  | 
| MX1, MX2, MX3, MX4, MX5, MX6, MX7, MX8, MX10, MX11, MX12, MX13, MX14, MX15, MX16, MX17, MX19, MX20, MX21, MX22 | 20 | MX-1U | MX-1U-MX_Alps_Hybrids | MX_Alps_Hybrid:MX-1U-NoLED |  |  |  | 
| MX9, MX18, MX23 | 3 | MX-2U | MX-1U-MX_Alps_Hybrids | MX_Alps_Hybrid:MX-2U-ReversedStabilizers-NoLED |  |  |  | 
| O1 | 1 | Outline | Conn_01x02 | locallib:outline | Generic connector, single row, 01x02, script generated (kicad-library-utils/schlib/autogen/connector/) |  |  | 
| SW1 | 1 | SW_Push | SW_Push | random-keyboard-parts:PushButton_6x6mm_TH_Pretty | Push button switch, generic, two pins |  |  | 
| U1 | 1 | ProMicro | ProMicro-promicro | promicro:ProMicro-EnforcedTop |  |  |  |

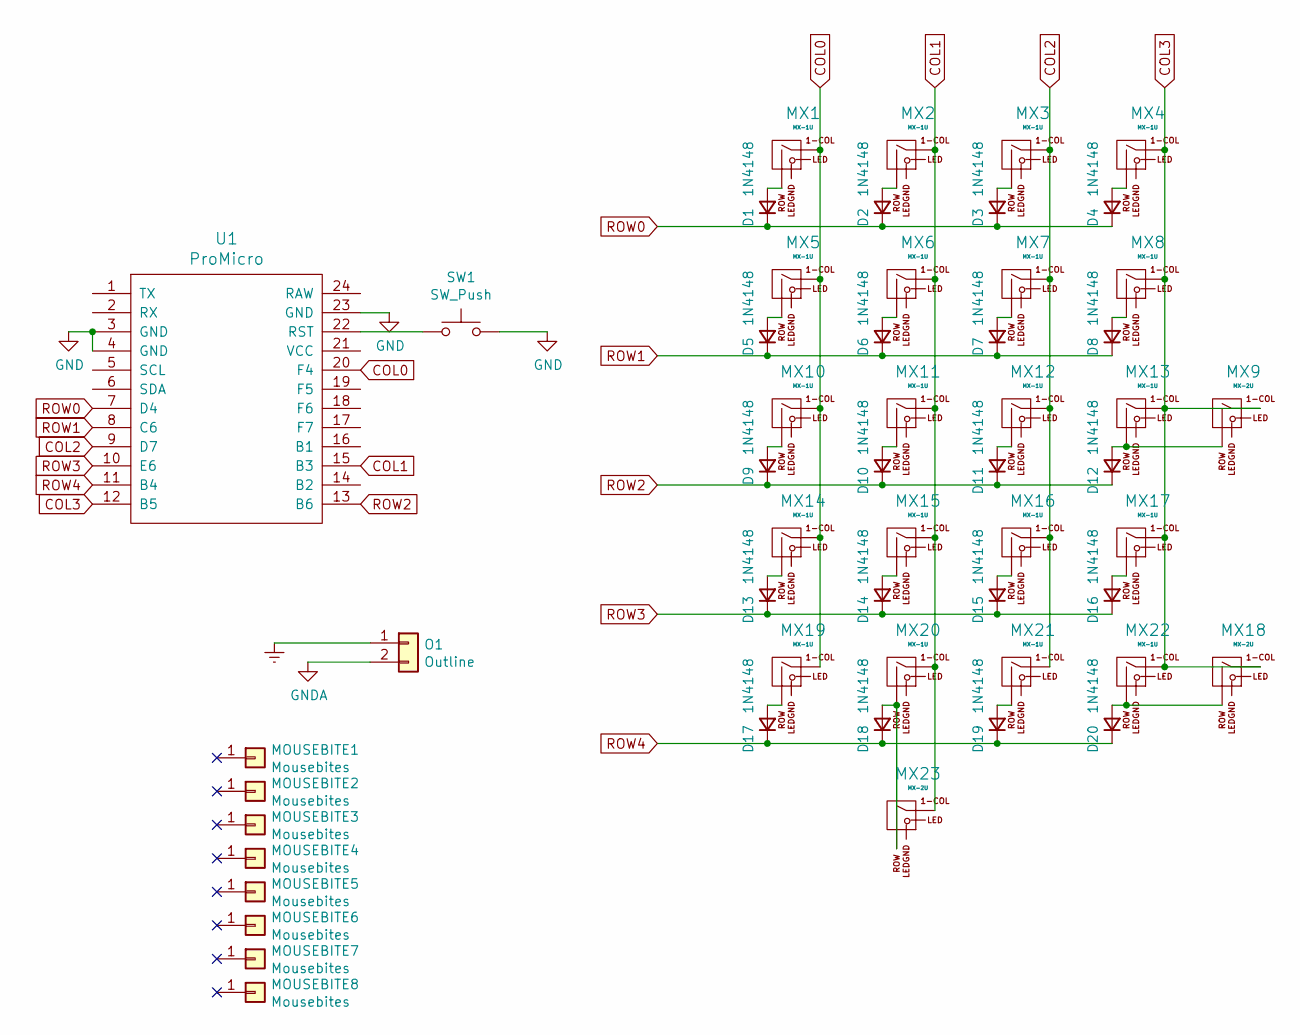
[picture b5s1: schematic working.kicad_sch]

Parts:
D1, D2, D3, D4, D5, D6, D7, D8, D9, D10, D11, D12, D13, D14, D15, D16, D17, D18, D19, D20: 1N4148; D_DO-35_SOD27_P7.62mm_Horizontal
MOUSEBITE1, MOUSEBITE2, MOUSEBITE3, MOUSEBITE4, MOUSEBITE5, MOUSEBITE6, MOUSEBITE7, MOUSEBITE8: Mousebites; breakaway-mousebites
MX1, MX2, MX3, MX4, MX5, MX6, MX7, MX8, MX10, MX11, MX12, MX13, MX14, MX15, MX16, MX17, MX19, MX20, MX21, MX22: MX-1U; MX-1U-NoLED
MX9, MX18, MX23: MX-2U; MX-2U-ReversedStabilizers-NoLED
O1: Outline; outline
SW1: SW_Push; PushButton_6x6mm_TH_Pretty
U1: ProMicro; ProMicro-EnforcedTop

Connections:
COL0: MX1.1 (COL), MX5.1 (COL), MX10.1 (COL), MX14.1 (COL), MX19.1 (COL), U1.20 (F4)
COL1: MX2.1 (COL), MX6.1 (COL), MX11.1 (COL), MX15.1 (COL), MX20.1 (COL), MX23.1 (COL), U1.15 (B3)
COL2: MX3.1 (COL), MX7.1 (COL), MX12.1 (COL), MX16.1 (COL), MX21.1 (COL), U1.9 (D7)
COL3: MX4.1 (COL), MX8.1 (COL), MX9.1 (COL), MX13.1 (COL), MX17.1 (COL), MX18.1 (COL), MX22.1 (COL), U1.12 (B5)
Earth: O1.1
GND: SW1.2, U1.3 (GND), U1.4 (GND), U1.23 (GND)
GNDA: O1.2
unnamed: D1.2 (A), MX1.2 (ROW)
unnamed: D2.2 (A), MX2.2 (ROW)
unnamed: D3.2 (A), MX3.2 (ROW)
unnamed: D4.2 (A), MX4.2 (ROW)
unnamed: D5.2 (A), MX5.2 (ROW)
unnamed: D6.2 (A), MX6.2 (ROW)
unnamed: D7.2 (A), MX7.2 (ROW)
unnamed: D8.2 (A), MX8.2 (ROW)
unnamed: D9.2 (A), MX10.2 (ROW)
unnamed: D10.2 (A), MX11.2 (ROW)
unnamed: D11.2 (A), MX12.2 (ROW)
unnamed: D12.2 (A), MX9.2 (ROW), MX13.2 (ROW)
unnamed: D13.2 (A), MX14.2 (ROW)
unnamed: D14.2 (A), MX15.2 (ROW)
unnamed: D15.2 (A), MX16.2 (ROW)
unnamed: D16.2 (A), MX17.2 (ROW)
unnamed: D17.2 (A), MX19.2 (ROW)
unnamed: D18.2 (A), MX20.2 (ROW), MX23.2 (ROW)
unnamed: D19.2 (A), MX21.2 (ROW)
unnamed: D20.2 (A), MX18.2 (ROW), MX22.2 (ROW)
unnamed: SW1.1, U1.22 (RST)
ROW0: D1.1 (K), D2.1 (K), D3.1 (K), D4.1 (K), U1.7 (D4)
ROW1: D5.1 (K), D6.1 (K), D7.1 (K), D8.1 (K), U1.8 (C6)
ROW2: D9.1 (K), D10.1 (K), D11.1 (K), D12.1 (K), U1.13 (B6)
ROW3: D13.1 (K), D14.1 (K), D15.1 (K), D16.1 (K), U1.10 (E6)
ROW4: D17.1 (K), D18.1 (K), D19.1 (K), D20.1 (K), U1.11 (B4)
